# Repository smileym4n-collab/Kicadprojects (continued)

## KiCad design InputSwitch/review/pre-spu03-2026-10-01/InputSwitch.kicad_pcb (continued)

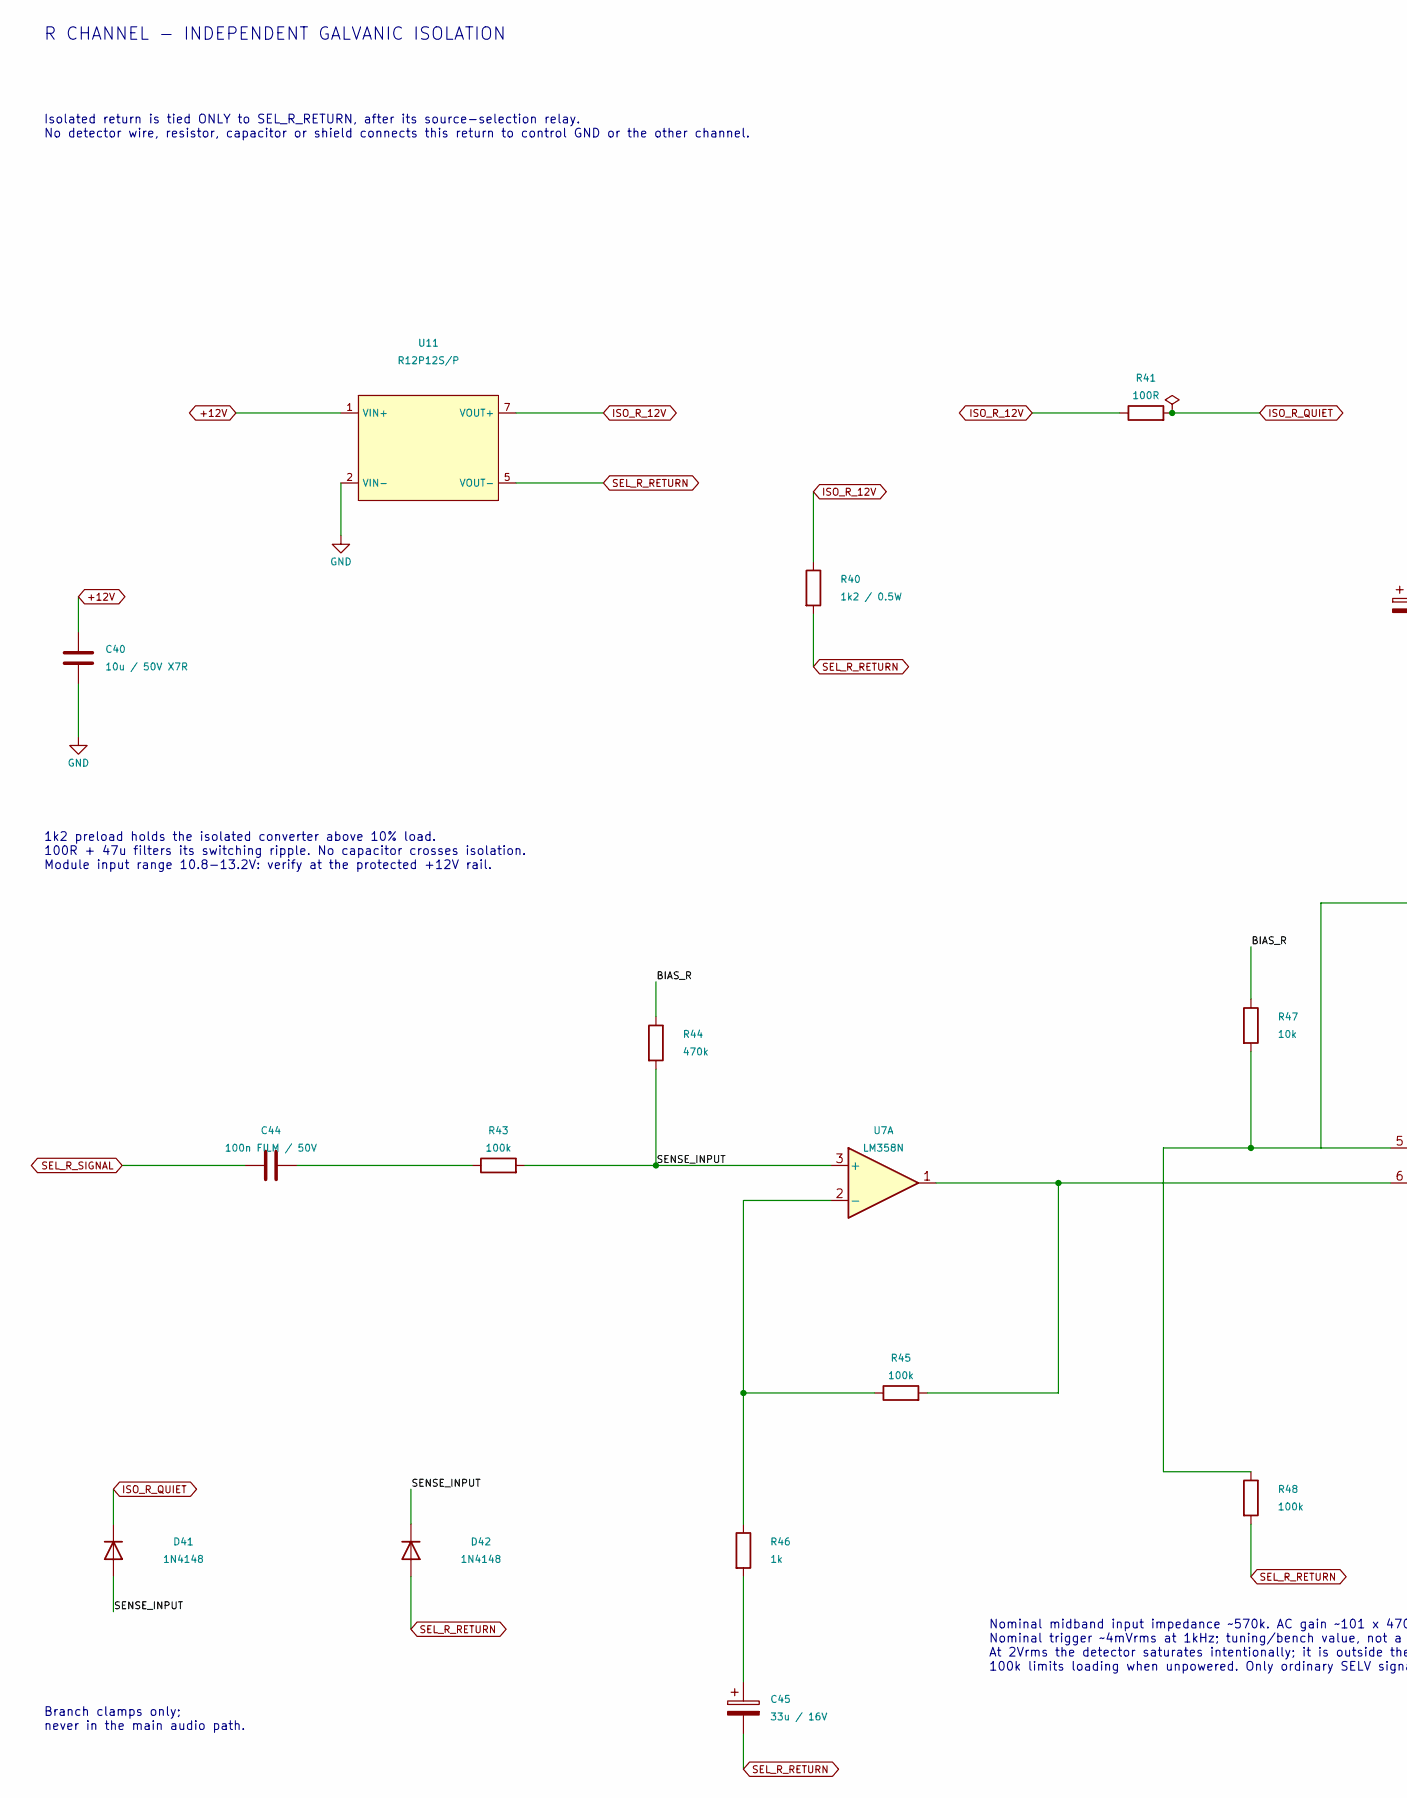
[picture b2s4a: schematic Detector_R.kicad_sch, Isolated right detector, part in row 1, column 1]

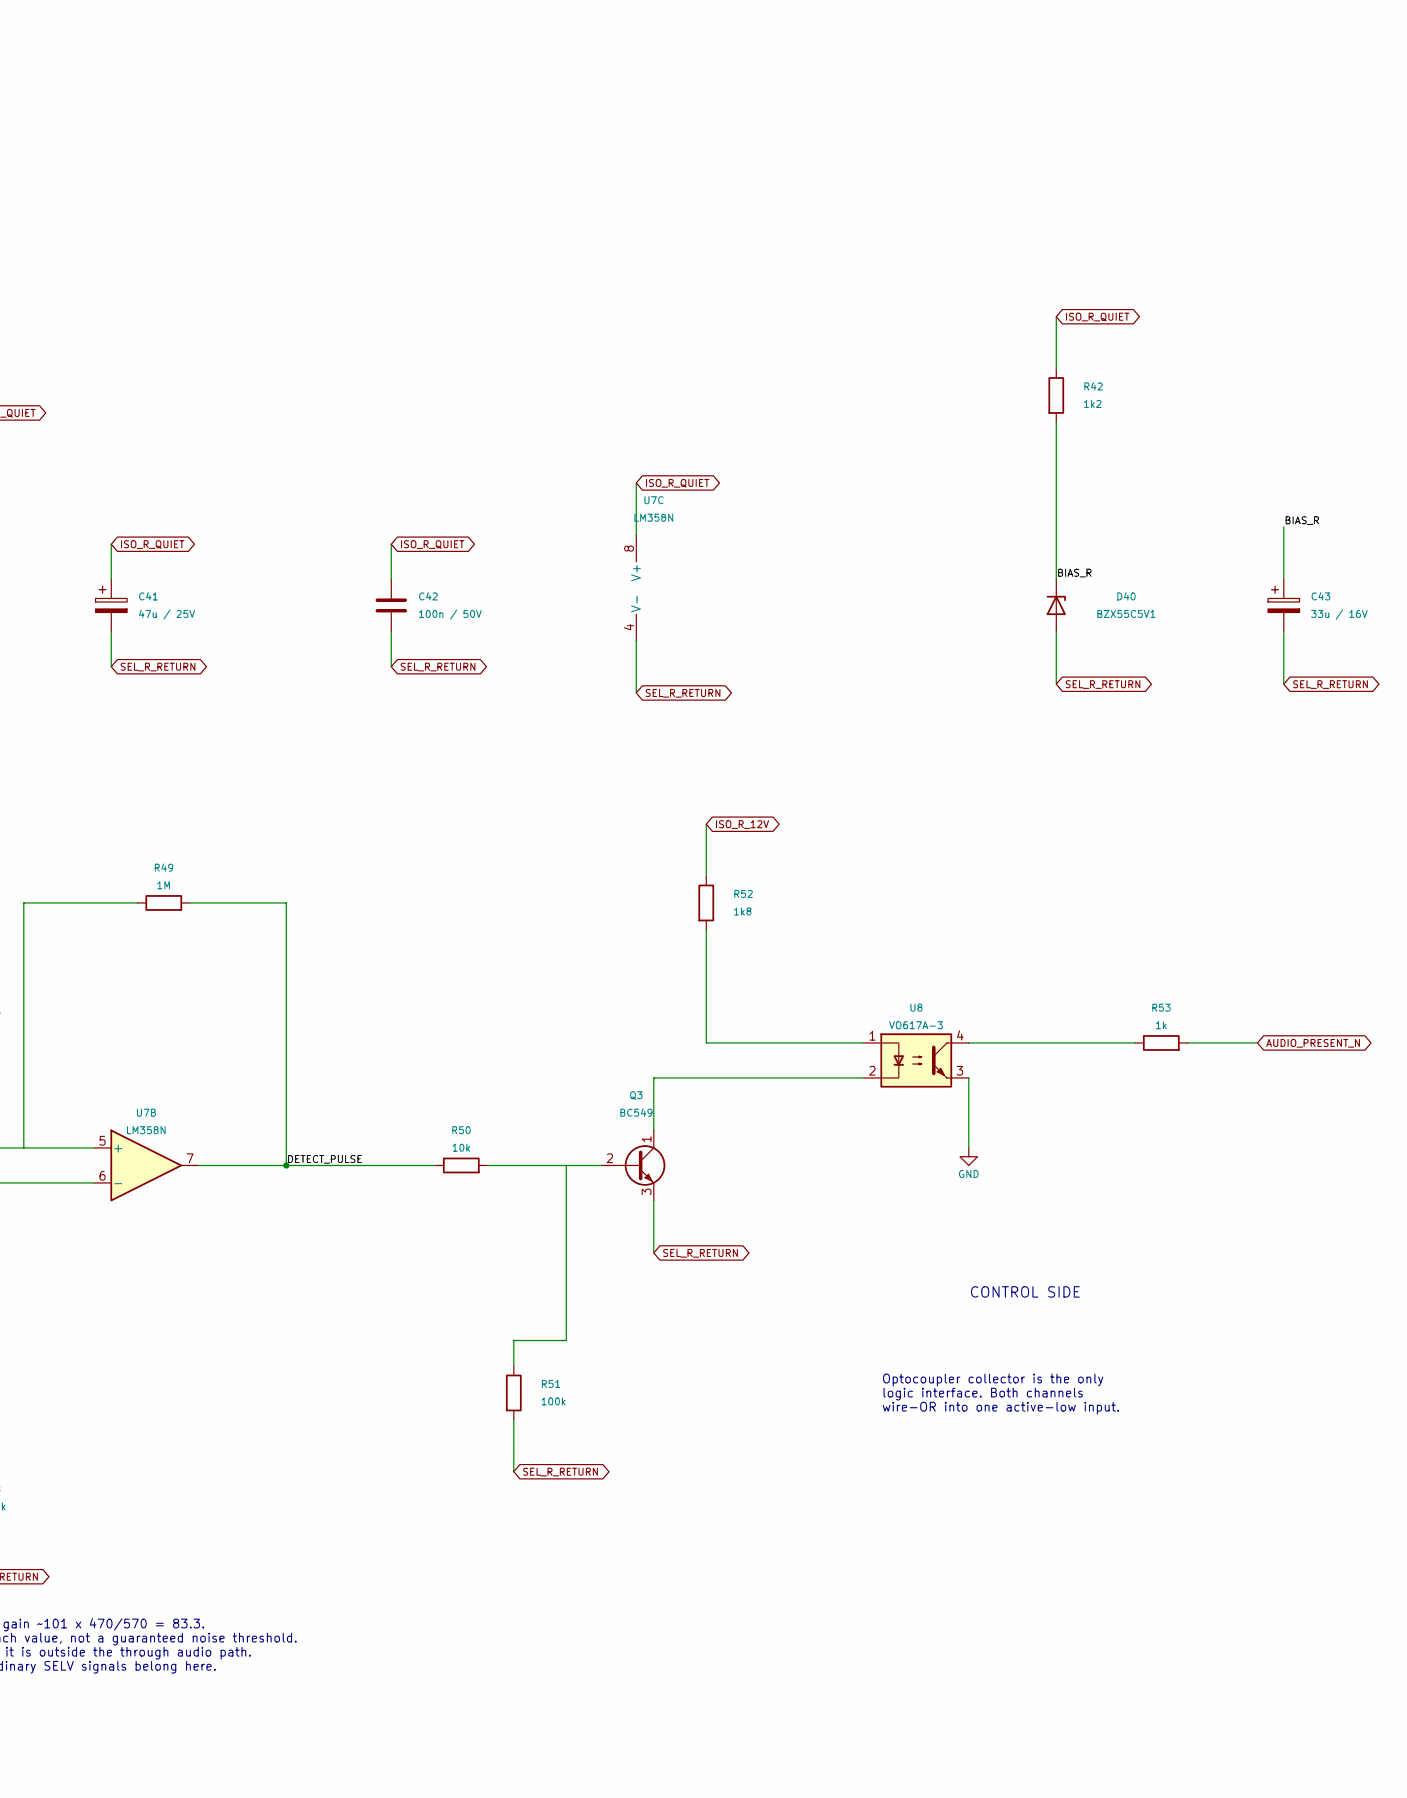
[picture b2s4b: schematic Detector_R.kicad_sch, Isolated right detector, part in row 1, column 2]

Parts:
C40: 10u / 50V X7R; C_0805_2012Metric_Pad1.18x1.45mm_HandSolder
C41: 47u / 25V; CP_Radial_D5.0mm_P2.50mm
C42: 100n / 50V; C_0805_2012Metric_Pad1.18x1.45mm_HandSolder
C43, C45: 33u / 16V; CP_Radial_D5.0mm_P2.50mm
C44: 100n FILM / 50V; C_Rect_L7.0mm_W2.0mm_P5.00mm
D40: BZX55C5V1; D_DO-35_SOD27_P7.62mm_Horizontal
D41, D42: 1N4148; D_DO-35_SOD27_P7.62mm_Horizontal
Q3: BC549; TO-92_Inline
R40: 1k2 / 0.5W; R_Axial_DIN0207_L6.3mm_D2.5mm_P10.16mm_Horizontal
R41: 100R; R_0805_2012Metric_Pad1.20x1.40mm_HandSolder
R42: 1k2; R_0805_2012Metric_Pad1.20x1.40mm_HandSolder
R43, R45, R48, R51: 100k; R_0805_2012Metric_Pad1.20x1.40mm_HandSolder
R44: 470k; R_0805_2012Metric_Pad1.20x1.40mm_HandSolder
R46, R53: 1k; R_0805_2012Metric_Pad1.20x1.40mm_HandSolder
R47, R50: 10k; R_0805_2012Metric_Pad1.20x1.40mm_HandSolder
R49: 1M; R_0805_2012Metric_Pad1.20x1.40mm_HandSolder
R52: 1k8; R_0805_2012Metric_Pad1.20x1.40mm_HandSolder
U7: LM358N; DIP-8_W7.62mm
U8: VO617A-3; DIP-4_W7.62mm
U11: R12P12S/P; R12P12S_P_SIP7

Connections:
/Isolated right detector/BIAS_R: C43.1, D40.1 (K), R42.2, R44.1, R47.1
/Isolated right detector/DETECT_PULSE: R49.2, R50.1, U7.7
/Isolated right detector/SENSE_INPUT: D41.2 (A), D42.1 (K), R43.2, R44.2, U7.3 (+)
AUDIO_PRESENT_N: R53.2; also elsewhere on the board
GND: C40.2, U8.3, U11.2 (VIN-); also elsewhere on the board
ISO_R_12V: R40.1, R41.1, R52.1, U11.7 (VOUT+)
ISO_R_QUIET: C41.1, C42.1, D41.1 (K), R41.2, R42.1, U7.8 (V+)
unnamed: C44.2, R43.1
unnamed: C45.1, R46.2
unnamed: Q3.2 (B), R50.2
unnamed: Q3.1 (C), U8.2
unnamed: R52.2, U8.1
unnamed: R53.1, U8.4
unnamed: R45.1, R46.1, U7.2 (-)
unnamed: R47.2, R48.1, U7.5 (+)
unnamed: R45.2, U7.1, U7.6 (-)
SEL_R_RETURN: C41.2, C42.2, C43.2, C45.2, D40.2 (A), D42.2 (A), Q3.3 (E), R40.2, R48.2, R51.2, U7.4 (V-), U11.5 (VOUT-); also elsewhere on the board
SEL_R_SIGNAL: C44.1; also elsewhere on the board

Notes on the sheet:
Branch clamps only; never in the main audio path.
Optocoupler collector is the only logic interface. Both channels wire-OR into one active-low input.
Isolated return is tied ONLY to SEL_R_RETURN, after its source-selection relay. No detector wire, resistor, capacitor or shield connects this return to control GND or the other channel.
CONTROL SIDE
R CHANNEL - INDEPENDENT GALVANIC ISOLATION
Nominal midband input impedance ~570k. AC gain ~101 x 470/570 = 83.3. Nominal trigger ~4mVrms at 1kHz; tuning/bench value, not a guaranteed noise threshold. At 2Vrms the detector saturates intentionally; it is outside the through audio path. 100k limits loading when unpowered. Only ordinary SELV si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
1k2 preload holds the isolated converter above 10% load. 100R + 47u filters its switching ripple. No capacitor crosses isolation. Module input range 10.8-13.2V: verify at the protected +12V rail.

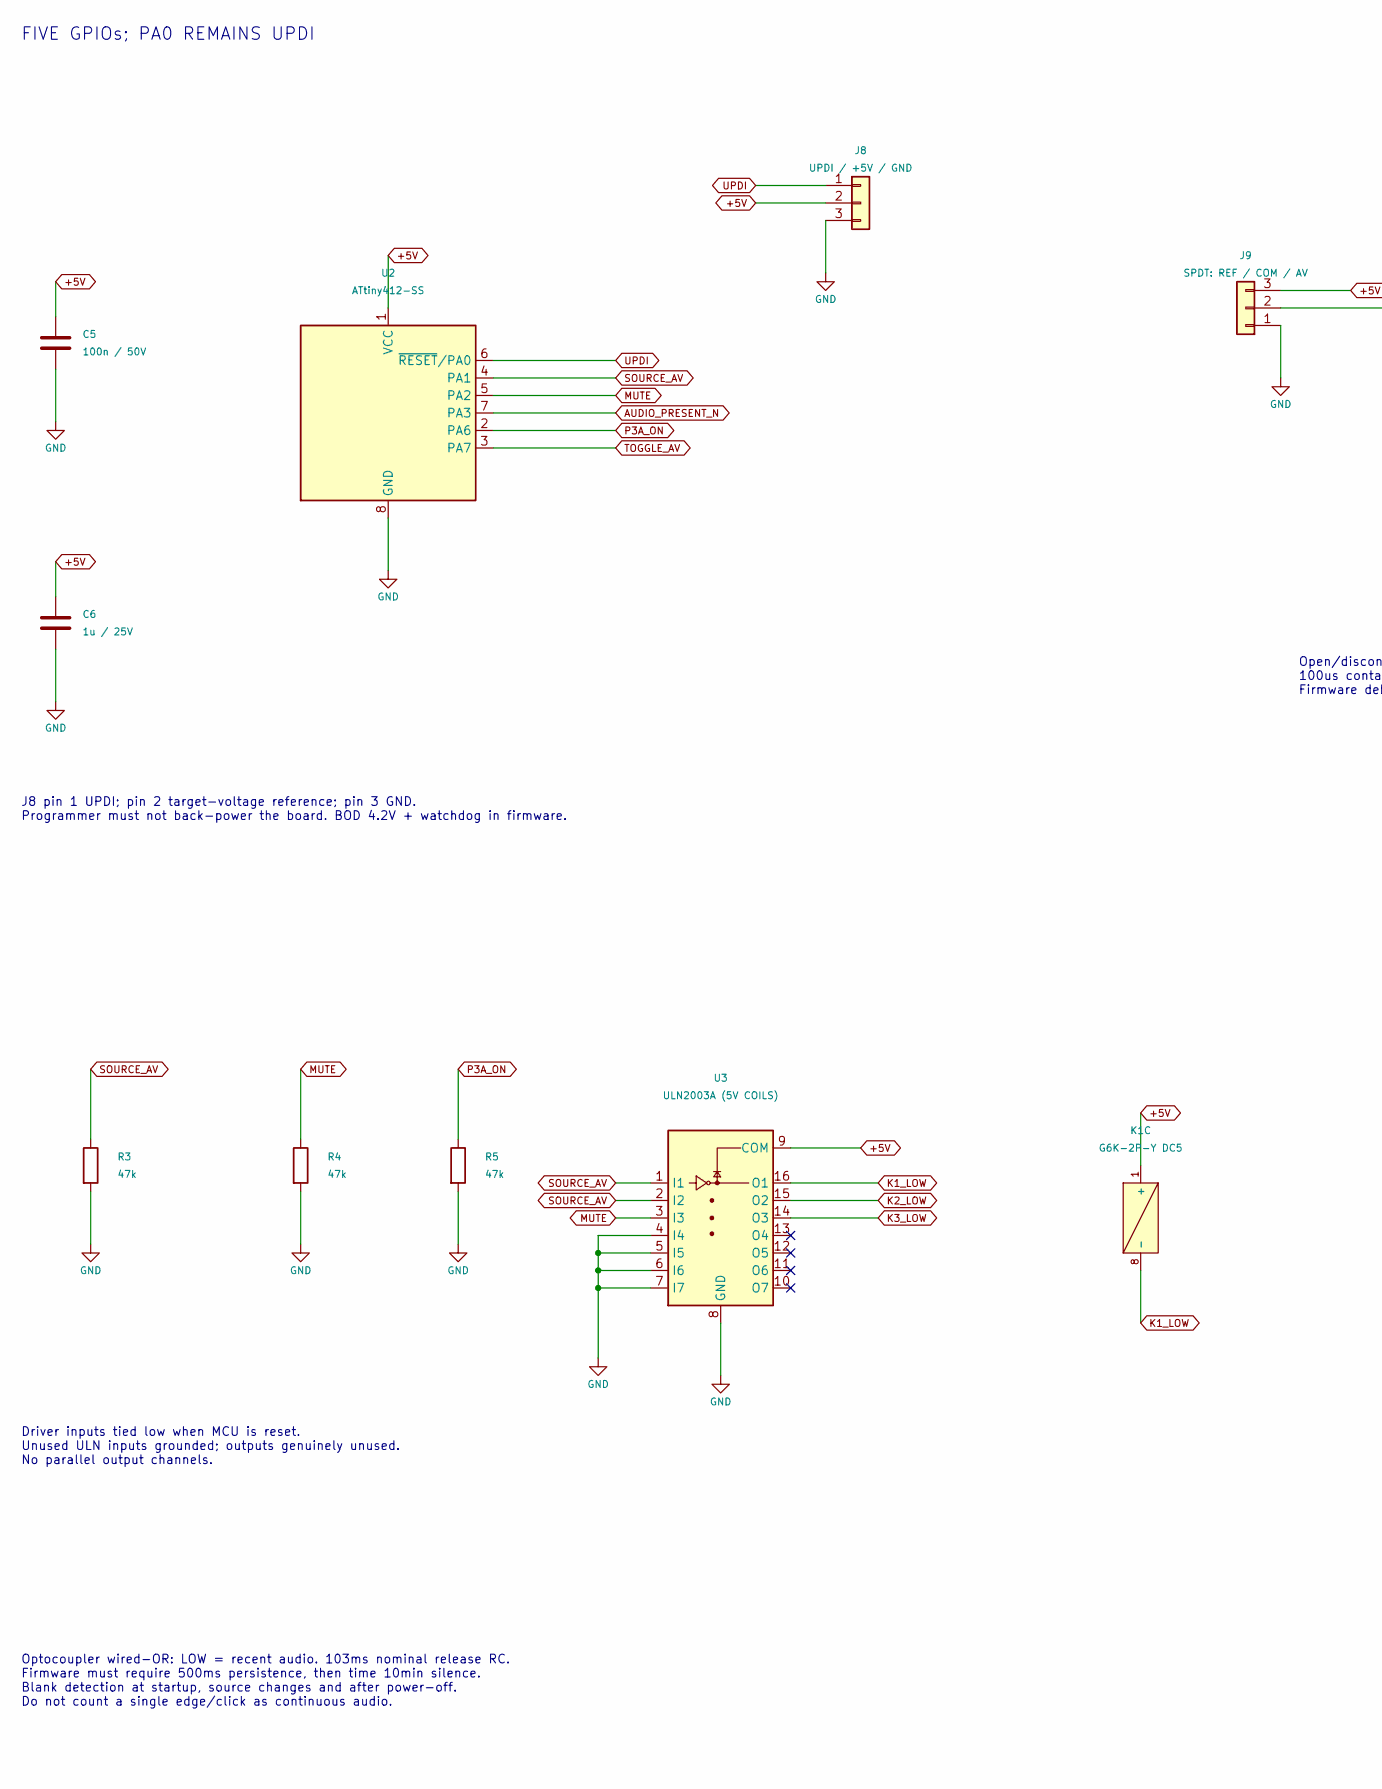
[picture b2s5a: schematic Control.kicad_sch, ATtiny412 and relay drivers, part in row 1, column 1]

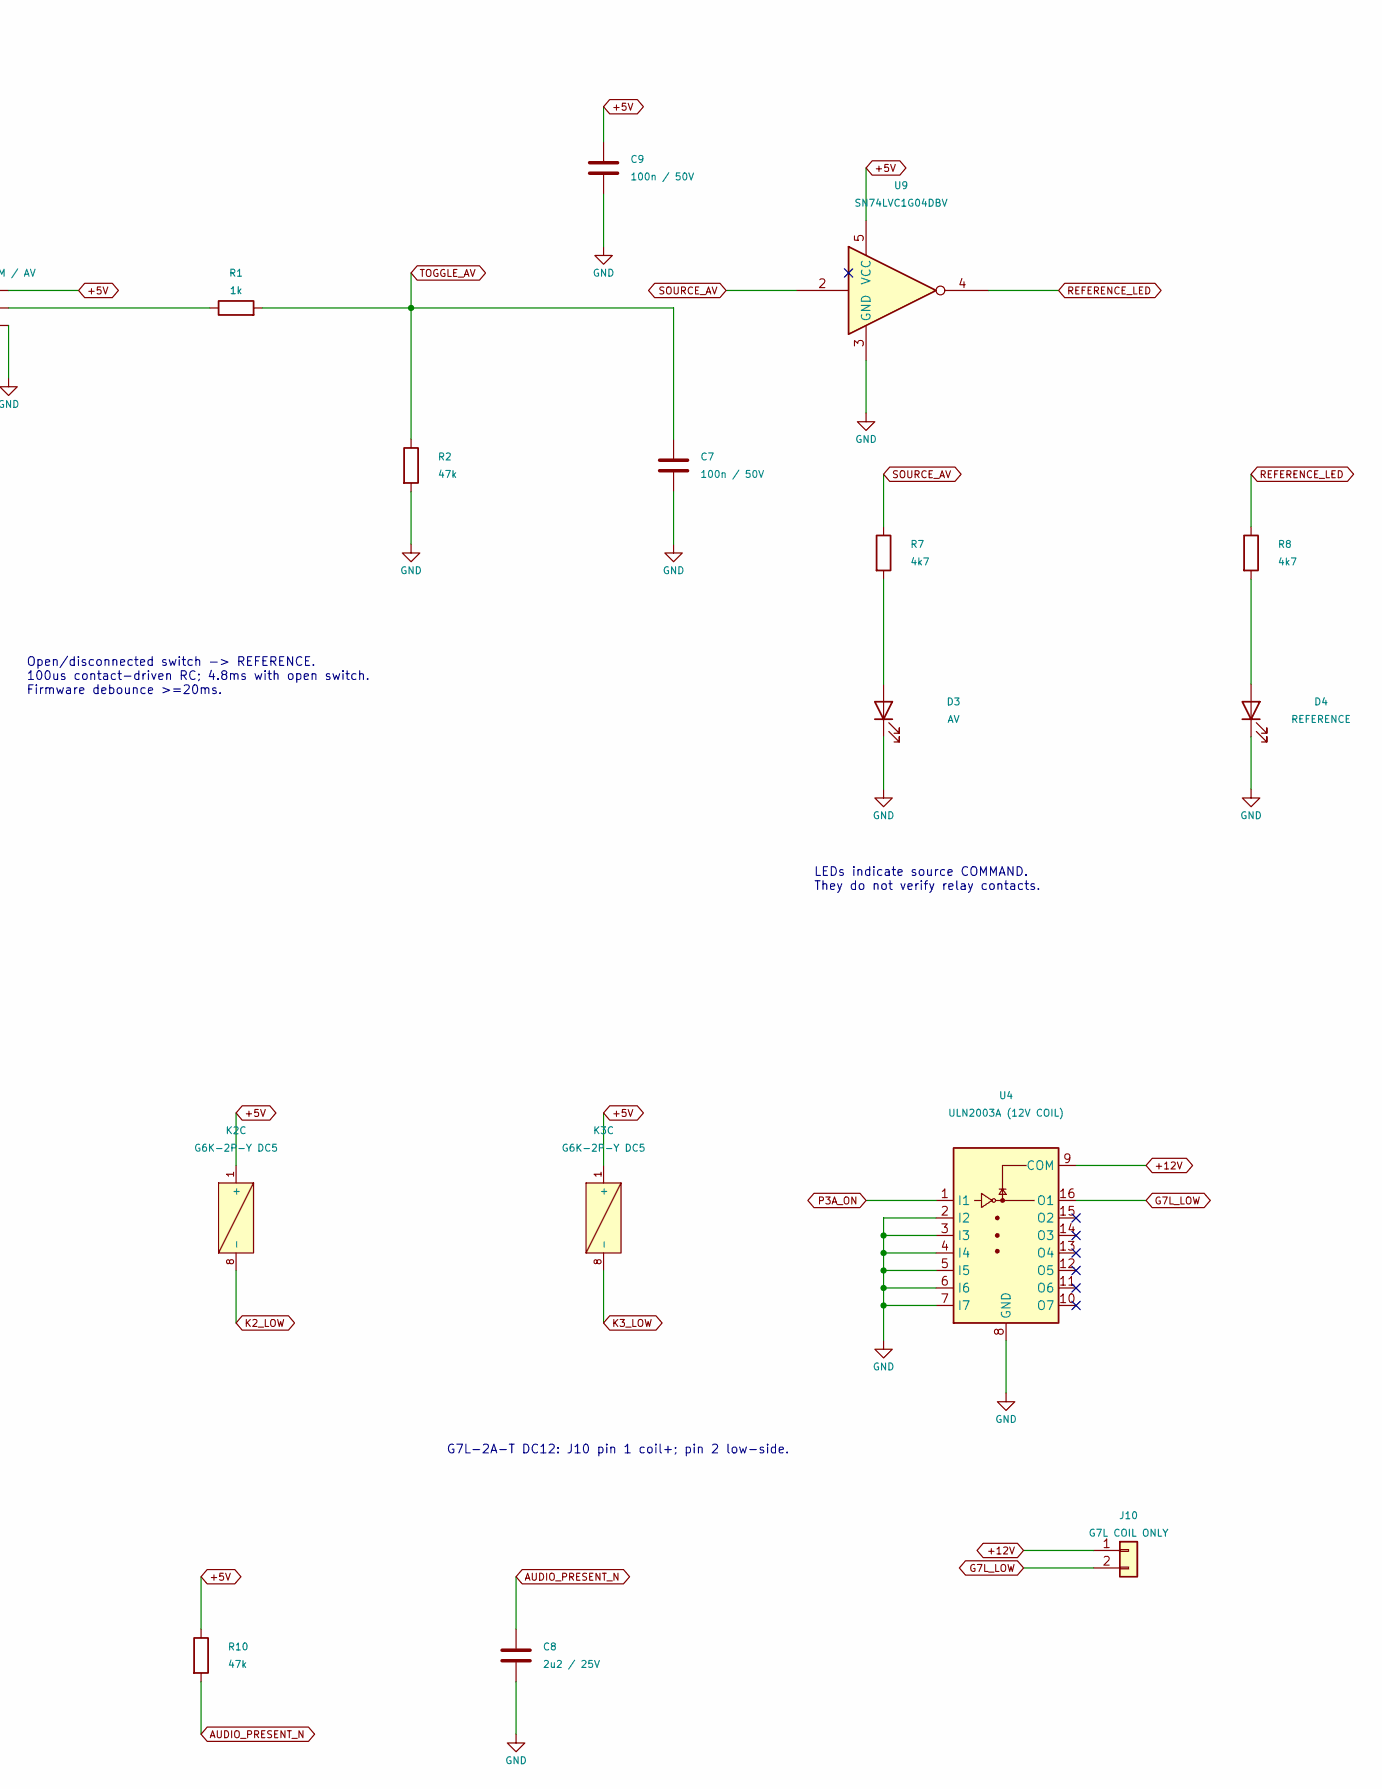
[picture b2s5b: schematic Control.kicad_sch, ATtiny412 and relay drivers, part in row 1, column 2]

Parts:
C5, C7, C9: 100n / 50V; C_0805_2012Metric_Pad1.18x1.45mm_HandSolder
C6: 1u / 25V; C_0805_2012Metric_Pad1.18x1.45mm_HandSolder
C8: 2u2 / 25V; C_0805_2012Metric_Pad1.18x1.45mm_HandSolder
D3: AV; LED_D3.0mm
D4: REFERENCE; LED_D3.0mm
J8: UPDI / +5V / GND; JST_XH_B3B-XH-A_1x03_P2.50mm_Vertical
J9: SPDT: REF / COM / AV; JST_XH_B3B-XH-A_1x03_P2.50mm_Vertical
J10: G7L COIL ONLY; JST_XH_B2B-XH-A_1x02_P2.50mm_Vertical
K1, K2, K3: G6K-2P-Y DC5; Relay_DPDT_Omron_G6K-2P-Y
R1: 1k; R_0805_2012Metric_Pad1.20x1.40mm_HandSolder
R2, R3, R4, R5, R10: 47k; R_0805_2012Metric_Pad1.20x1.40mm_HandSolder
R7, R8: 4k7; R_0805_2012Metric_Pad1.20x1.40mm_HandSolder
U2: ATtiny412-SS; SOIC-8_3.9x4.9mm_P1.27mm
U3: ULN2003A (5V COILS); SOIC-16_3.9x9.9mm_P1.27mm
U4: ULN2003A (12V COIL); SOIC-16_3.9x9.9mm_P1.27mm
U9: SN74LVC1G04DBV; SOT-23-5

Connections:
+5V: C5.1, C6.1, C9.1, J8.2, J9.3, K1.1 (+), K2.1 (+), K3.1 (+), R10.1, U2.1 (VCC), U3.9 (COM), U9.5 (VCC); also elsewhere on the board
AUDIO_PRESENT_N: C8.1, R10.2, U2.7 (PA3); also elsewhere on the board
G7L_LOW: J10.2, U4.16 (O1)
GND: C5.2, C6.2, C7.2, C8.2, C9.2, D3.1 (K), D4.1 (K), J8.3, J9.1, R2.2, R3.2, R4.2, R5.2, U2.8 (GND), U3.4 (I4), U3.5 (I5), U3.6 (I6), U3.7 (I7), U3.8 (GND), U4.2 (I2), U4.3 (I3), U4.4 (I4), U4.5 (I5), U4.6 (I6), U4.7 (I7), U4.8 (GND), U9.3 (GND); also elsewhere on the board
K1_LOW: K1.8 (-), U3.16 (O1)
K2_LOW: K2.8 (-), U3.15 (O2)
K3_LOW: K3.8 (-), U3.14 (O3)
MUTE: R4.1, U2.5 (PA2), U3.3 (I3)
unnamed: D3.2 (A), R7.2
unnamed: D4.2 (A), R8.2
unnamed: J9.2, R1.1
P3A_ON: R5.1, U2.2 (PA6), U4.1 (I1)
REFERENCE_LED: R8.1, U9.4
SOURCE_AV: R3.1, R7.1, U2.4 (PA1), U3.1 (I1), U3.2 (I2), U9.2
TOGGLE_AV: C7.1, R1.2, R2.1, U2.3 (PA7)
UPDI: J8.1, U2.6 (~RESET/PA0)

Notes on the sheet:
J8 pin 1 UPDI; pin 2 target-voltage reference; pin 3 GND. Programmer must not back-power the board. BOD 4.2V + watchdog in firmware.
FIVE GPIOs; PA0 REMAINS UPDI
LEDs indicate source COMMAND. They do not verify relay contacts.
G7L-2A-T DC12: J10 pin 1 coil+; pin 2 low-side.
Driver inputs tied low when MCU is reset. Unused ULN inputs grounded; outputs genuinely unused. No parallel output channels.
Open/disconnected switch -> REFERENCE. 100us contact-driven RC; 4.8ms with open switch. Firmware debounce >=20ms.
Optocoupler wired-OR: LOW = recent audio. 103ms nominal release RC. Firmware must require 500ms persistence, then time 10min silence. Blank detection at startup, source changes and after power-off. Do not count a single edge/click as continuous audio.

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
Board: 2 copper layers, 99 parts (0 on the bottom side), 61 nets, no tracks yet.

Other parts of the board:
TP1: +12V; TestPoint_THTPad_D2.0mm_Drill1.0mm
TP2: +5V; TestPoint_THTPad_D2.0mm_Drill1.0mm
TP3: GND; TestPoint_THTPad_D2.0mm_Drill1.0mm

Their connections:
+5V: TP2.1 (1_1); also elsewhere on the board
GND: TP3.1 (1_1); also elsewhere on the board

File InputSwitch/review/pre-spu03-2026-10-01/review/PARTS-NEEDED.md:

# InputSwitch parts needed

Inventory was checked live during this review. No stock was reserved or consumed and no orders were placed. Quantities listed as available are inventory records, not physical inspection. Match package and suffix exactly before assembly.

## Main purchases not found in inventory

| Qty | Part | Purpose / package |
|---:|---|---|
| 2 | RECOM **R12P12S/P** | Independent 12 V to isolated 12 V supplies; standard SIP7 pinout, populated pins 1/2/5/7. Do not buy /X2 for this footprint. |
| 2 | Vishay **VO617A-3** | Detector optocouplers; standard DIP-4, 7.62 mm row spacing. |
| 1 | RECOM **R-78E5.0-0.5** | 12 V to 5 V buck module, SIP3, 500 mA. |
| 1 | TI **SN74LVC1G04DBVR** | Source-LED inverter, DBV / SOT-23-5. |
| 2 | Vishay **BZX55C5V1** | 5.1 V detector references, DO-35. |
| 1 | Vishay **SS14** | Reverse-polarity blocking diode, SMA. No inventory hit in the initial search. |
| 1 | Littelfuse **SMBJ13A** | Unidirectional input TVS, SMB. |
| 1 | Omron **G7L-2A-T DC12** | External mains relay; no inventory record found. Omit purchase if already physically owned. |

The isolated modules are the principal extra parts required by the two-channel isolation decision. The inventory's three “SPI03L-05” modules were **not substituted**: their model text and linked SPU03 datasheet are inconsistent and their suitability was not established.

Supplier listings: [R12P12S/P at Mouser](https://www.mouser.com/en/ProductDetail/RECOM-Power/R12P12S-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, [VO617A-3 at DigiKey UK](https://www.digikey.co.uk/en/products/detail/vishay-semicond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, [R-78E5.0-0.5 manufacturer page](https://recom-power.com/en/products/switching-regulators/swi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 These establish catalogue presence, not guaranteed current UK stock, price or lead time. Confirm availability before ordering; /P and /P/X2 are not interchangeable.

## Reuse from recorded stock

| Need | Inventory record | Recorded stock | Package / location |
|---:|---|---:|---|
| 3 | G6K-2P-Y, 5 V, ID 420 | 4, none reserved | Through-hole; location not recorded |
| 1 | ATtiny412, ID 80 | 6, none reserved | SOIC-8; SMD Parts |
| 2 | ULN2003A, ID 121 | 7, none reserved | ST SOIC-16; SMD Parts |
| 2 | LM358, ID 389 | 2, none reserved | TI DIP-8; Opamp drawer |
| 2 | BC549, ID 452 | 117, none reserved | TO-92; manufacturer/location not recorded |
| 4 | 1N4148, ID 138 | 63, none reserved | Through-hole; Parts drawer 2 |

The five DIP-16 ULN2003As (ID 120, Mixed ICs drawer) are not the package assigned in this schematic. Use the SOIC-16 stock above unless a package change is approved. Check the physical G6K markings really say DC5 and the BC549 lead order is C-B-E before assembly. The two LM358s use the entire recorded unreserved quantity.

## Other build items

- Six two-pin JST XH headers for audio and two more for DC input/G7L coil; two three-pin JST XH headers for UPDI and toggle, with matching housings/crimps.
- SPDT ON-ON front toggle, two suitable indicator LEDs, six isolated RCA sockets or existing system harnesses, shielded audio wiring.
- Regulated isolated 12 V wall adapter, preferably ±2%, at least 0.5 A; suitable DC inlet/cable.
- T500mA 5 x 20 mm fuse and holder. **Holder provision needs mechanical confirmation:** the assigned FX0457 library footprint and Bulgin's conflicting online orientation descriptions need comparison with the actual part/drawing before purchase/layout.
- Three test-point pins/pads and existing mounting hardware.
- Passives listed below; check drawer stock by exact value/rating before buying. SMD resistors and ceramics are **2012 metric**. The two 1k2 preload resistors are through-hole, at least 0.5 W. Use 1% resistors; thin-film in detector gain/threshold networks is sensible. No precision parts are needed in utility pull-downs or LED feeds.
- Main input capacitor C1: 100 µF / 35 V, 6.3 mm body, 2.5 mm lead spacing provision. Other radial electrolytics currently use 5 mm body / 2.5 mm pitch provisions. Confirm exact bought capacitor dimensions. C24/C44 are detector-branch film capacitors; their 5 mm pitch / body provision also needs an exact-part fit check.

The following grouped BOM is generated from the final exported netlist, so quantities and references correspond to the schematic. It is an assembly planning BOM, not an order-ready manufacturer-part-number BOM.

| Qty | Value / part | References | Package / provision |
|---:|---|---|---|
| 1 | +12V | TP1 | TestPoint_THTPad_D2.0mm_Drill1.0mm |
| 1 | +5V | TP2 | TestPoint_THTPad_D2.0mm_Drill1.0mm |
| 2 | 100R | R21, R41 | 2012 metric |
| 8 | 100k | R23, R25, R28, R31, R43, R45, R48, R51 | 2012 metric |
| 6 | 100n / 50V | C4, C5, C7, C9, C22, C42 | 2012 metric |
| 2 | 100n FILM / 50V | C24, C44 | C_Rect_L7.0mm_W2.0mm_P5.00mm |
| 1 | 100u / 35V | C1 | CP_Radial_D6.3mm_P2.50mm |
| 4 | 10k | R27, R30, R47, R50 | 2012 metric |
| 3 | 10u / 50V X7R | C2, C20, C40 | 2012 metric |
| 1 | 12V DC INPUT | J7 | JST_XH_B2B-XH-A_1x02_P2.50mm_Vertical |
| 2 | 1M | R29, R49 | 2012 metric |
| 4 | 1N4148 | D21, D22, D41, D42 | D_DO-35_SOD27_P7.62mm_Horizontal |
| 5 | 1k | R1, R26, R33, R46, R53 | 2012 metric |
| 2 | 1k2 | R22, R42 | 2012 metric |
| 2 | 1k2 / 0.5W | R20, R40 | R_Axial_DIN0207_L6.3mm_D2.5mm_P10.16mm_Horizontal |
| 2 | 1k8 | R32, R52 | 2012 metric |
| 1 | 1u / 25V | C6 | 2012 metric |
| 1 | 2u2 / 25V | C8 | 2012 metric |
| 4 | 33u / 16V | C23, C25, C43, C45 | CP_Radial_D5.0mm_P2.50mm |
| 2 | 470k | R24, R44 | 2012 metric |
| 5 | 47k | R2, R3, R4, R5, R10 | 2012 metric |
| 1 | 47u / 16V | C3 | CP_Radial_D5.0mm_P2.50mm |
| 2 | 47u / 25V | C21, C41 | CP_Radial_D5.0mm_P2.50mm |
| 2 | 4k7 | R7, R8 | 2012 metric |
| 1 | ATtiny412-SS | U2 | SOIC-8_3.9x4.9mm_P1.27mm |
| 1 | AV | D3 | LED_D3.0mm |
| 1 | AV L | J2 | JST_XH_B2B-XH-A_1x02_P2.50mm_Vertical |
| 1 | AV R | J4 | JST_XH_B2B-XH-A_1x02_P2.50mm_Vertical |
| 2 | BC549 | Q2, Q3 | TO-92_Inline |
| 2 | BZX55C5V1 | D20, D40 | D_DO-35_SOD27_P7.62mm_Horizontal |
| 3 | G6K-2P-Y DC5 | K1, K2, K3 | Relay_DPDT_Omron_G6K-2P-Y |
| 1 | G7L COIL ONLY | J10 | JST_XH_B2B-XH-A_1x02_P2.50mm_Vertical |
| 1 | GND | TP3 | TestPoint_THTPad_D2.0mm_Drill1.0mm |
| 2 | LM358N | U5, U7 | DIP-8_W7.62mm |
| 4 | M4 | H1, H2, H3, H4 | MountingHole_4.3mm_M4 |
| 1 | P3A L | J5 | JST_XH_B2B-XH-A_1x02_P2.50mm_Vertical |
| 1 | P3A R | J6 | JST_XH_B2B-XH-A_1x02_P2.50mm_Vertical |
| 1 | R-78E5.0-0.5 | U1 | Converter_DCDC_RECOM_R-78E-0.5_THT |
| 2 | R12P12S/P | U10, U11 | R12P12S_P_SIP7 |
| 1 | REFERENCE | D4 | LED_D3.0mm |
| 1 | REFERENCE L | J1 | JST_XH_B2B-XH-A_1x02_P2.50mm_Vertical |
| 1 | REFERENCE R | J3 | JST_XH_B2B-XH-A_1x02_P2.50mm_Vertical |
| 1 | SMBJ13A | D2 | D_SMB |
| 1 | SN74LVC1G04DBV | U9 | SOT-23-5 |
| 1 | SPDT: REF / COM / AV | J9 | JST_XH_B3B-XH-A_1x03_P2.50mm_Vertical |
| 1 | SS14 | D1 | D_SMA |
| 1 | T500mA | F1 | Fuseholder_Cylinder-5x20mm_Bulgin_FX0457_Horizontal_Closed |
| 1 | ULN2003A (12V COIL) | U4 | SOIC-16_3.9x9.9mm_P1.27mm |
| 1 | ULN2003A (5V COILS) | U3 | SOIC-16_3.9x9.9mm_P1.27mm |
| 1 | UPDI / +5V / GND | J8 | JST_XH_B3B-XH-A_1x03_P2.50mm_Vertical |
| 2 | VO617A-3 | U6, U8 | DIP-4_W7.62mm |
